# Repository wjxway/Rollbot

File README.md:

# Rollbot: a Spherical Robot Driven by a Single Actuator

Paper can be fetched from [Arxiv](https://arxiv.org/abs/2404.05120).

This repo is the full implementation of Rollbot, including complete hardware, software, theoretical derivation files.

It's still under construction, so the files might be a bit messy. I will clean it up once the paper is officially accepted.

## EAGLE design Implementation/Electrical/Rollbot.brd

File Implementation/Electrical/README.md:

This is just a power converter from 4s battery down to 3.3V. Feel free to create your own.

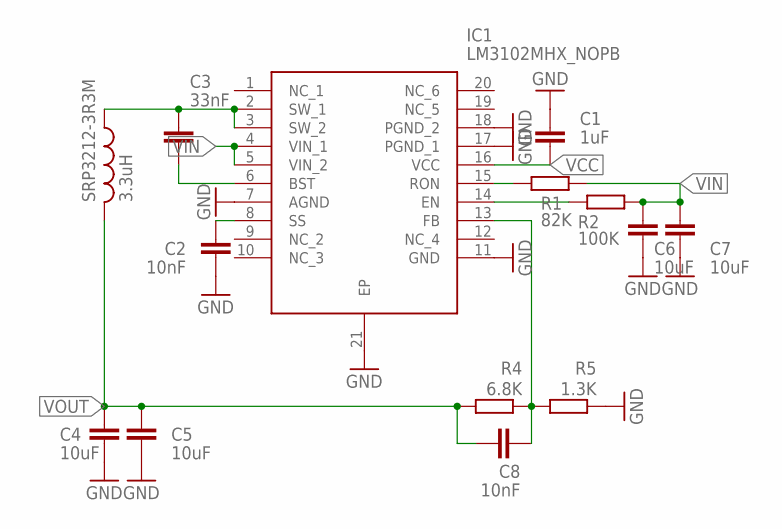
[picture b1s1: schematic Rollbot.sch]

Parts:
C1: 1uF; C0603
C2, C8: 10nF; C0603
C3: 33nF; C0603
C4, C5, C6, C7: 10uF; C0603
IC1: LM3102MHX_NOPB; SOP65P640X110-21N
R1: 82K; R0603
R2: 100K; R0603
R4: 6.8K; R0603
R5: 1.3K; R0603
SRP3212-3R3M: 3.3uH; SRP3212

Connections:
GND: C1.1, C2.1, C4.2, C5.2, C6.2, C7.2, IC1.7 (AGND), IC1.11 (GND), IC1.17 (PGND_1), IC1.18 (PGND_2), IC1.21 (EP), R5.1
unnamed: IC1.14 (EN), R2.1
unnamed: C3.1, IC1.2 (SW_1), IC1.3 (SW_2), SRP3212-3R3M.P$1 (1)
unnamed: C8.2, IC1.13 (FB), R4.1, R5.2
unnamed: C3.2, IC1.6 (BST)
unnamed: C2.2, IC1.8 (SS)
RON: IC1.15 (RON), R1.1
VCC: C1.2, IC1.16 (VCC)
VIN: C6.1, C7.1, IC1.4 (VIN_1), IC1.5 (VIN_2), R1.2, R2.2
VOUT: C4.1, C5.1, C8.1, R4.2, SRP3212-3R3M.P$2 (2)

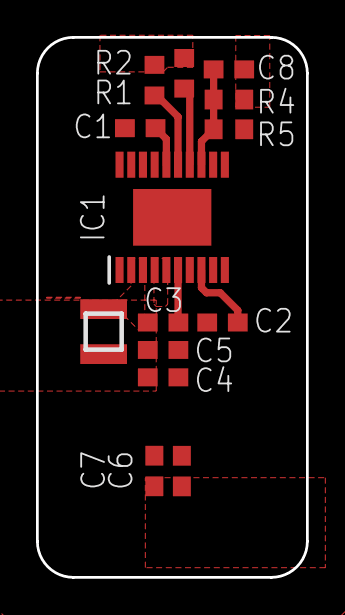
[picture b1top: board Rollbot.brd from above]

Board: 2 copper layers, 15.0 x 30.0 mm, 14 parts (0 on the bottom side), 10 nets.
